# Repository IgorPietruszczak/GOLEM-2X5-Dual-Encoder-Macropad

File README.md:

# 🎮 GOLEM 2x5 Dual Encoder Macropad

An open-source 2x5 macropad featuring **dual rotary encoders**, a custom PCB, and fully 3D-printed case.

---

## ✨ Features

- **2×5 key grid** — 10 programmable keys
- **Dual rotary encoders** — for volume, scrolling, zoom, or any custom action
- **Pro Micro** microcontroller (ATmega32U4)
- **QMK firmware** — customizable layers, macros, and encoder mappings
- **Custom KiCad PCB** — open-source design files included
- **3D-printed case** — print-ready STL files included
- **MIT licensed** — free to use, modify, and share

---

## 📁 Repository Structure

```
GOLEM-2X5-Dual-Encoder-Macropad/
├── 3D Parts/                           # STL files for the case and knobs
├── Design Files For 3D Parts/          # KiCad schematics and PCB layout
├── PCB Design & Production files/      # Supporting design assets
├── QMK Keyboard Layout/                # QMK firmware source
├── LICENSE
└── README.md
```

---

## 🛒 Bill of Materials (BOM)

| Part | Quantity | Notes |
|------|----------|-------|
| Pro Micro (ATmega32U4) | 1 | USB-C version recommended |
| Rotary Encoder (EC11) | 2 | With push-button |
| Encoder Knobs | 2 | STL included, or use off-the-shelf |
| MX-compatible switches | 10 | 3-pin |
| 1N4148 Diodes | 10 | Through-hole |
| Keycaps | 10 | MX compatible |
| M2 screws 5mm & heat inserts | — | For case assembly |
| Custom PCB | 1 | Gerber files in `PCB Design & Production files/` |
| 3D-printed case | 1 set | STL files in `3D Parts/` |
| Silicone anti-slip pads | 4 | Placed in the corners on the bottom of the case |
| Tact Switch | 1 | For easy enabling of boot mode |

---

## 🖨️ 3D Printing

All STL files are located in the `3D Parts/` folder.

**Recommended settings:**
- Layer height: **0.2 mm**
- Infill: **15%**
- Supports: **No** (parts are designed to print without supports)
- Material: **PLA or PETG**

**Parts to print:**
- `Case_bottom.3mf` — Main keyboard body × 1
- `Encoder_Support.3mf` — Support to prevent bending the PCB while pressing the encoder button × 1
- `Knob_Edit_105_scaled.stl` — Knob for the standard rotary encoder × 2
- `PCB_Cover.stl` — Top PCB cover × 1

> The encoder knob model is adapted from [this Thingiverse design](https://www.thingiverse.com/thing:4206617/) — scaled up 5% to better fit EC11 encoders.

---

## 🔌 PCB & Wiring

PCB design files (KiCad) are located in the `PCB Design & Production files/` folder.
Ready Gerber files are located in the **production** folder.
Order PCB boards from the PCB manufacturer of your choosing.

**To open the project:**
1. Install [KiCad](https://www.kicad.org/) (version 7.0 or later recommended)
2. Open `Design_Files/*.kicad_pro`
3. Review the schematic

> KiCad component library courtesy of [@joe_scotto](https://www.youtube.com/@joe_scotto/featured) — this project is heavily inspired by this creator.

---

## 🔧 Assembly Guide

1. **Solder diodes to PCB** — Pay attention to soldering them with the correct polarity. Check the KiCad project or PCB 3D model for reference.
2. **Solder Pro Micro to PCB** — The project is designed to use the pin arrays that come with the microcontroller. Check the PCB 3D model for reference.
3. **Solder tact switch to PCB.**
4. **Place MX switches into holes on PCB Cover 3D print** — Pay attention to placing them in the correct orientation.
5. **Solder MX switches to PCB** — After this step the PCB cover is unremovable, so be sure to complete all prior steps correctly.
6. **Solder 2 rotary encoders to PCB** — Make sure they sit flat and stable before soldering.
7. **Insert heat inserts into designated places on Bottom Cover.**
8. **Screw PCB to bottom cover with M2 screws.**
9. **Place keycaps on MX switches and knobs on rotary encoders.**
10. **Stick silicone pads to the bottom of the Bottom Cover.**

---

## ⚡ Firmware Setup (QMK)

This keyboard uses QMK firmware. Here are some tutorials on how to set up the keyboard layout:

- [Tutorial 1](https://www.youtube.com/watch?v=fuBJbdCFF0Q&t=241s)
- [Tutorial 2](https://www.youtube.com/watch?v=hjml-K-pV4E&t=1155s)

### Quick Setup

1. **Install QMK Firmware** — QMK MSYS, QMK Toolbox, drivers, etc.
2. **Move the keyboard layout** from `QMK Keyboard Layout/` to your keyboards folder in QMK.
3. **Flash the GOLEM 2x5 keyboard layout using QMK Toolbox** — Enable flash mode using the tact switch on the keyboard.
4. **Edit the keyboard layout (optional)** — Open `golem_2x5_dualencoder_macropad/` in a text editor and edit the keyboard settings.

---

## 🤝 Contributing

Contributions are welcome! Feel free to:
- Open an **Issue** for bugs or suggestions
- Submit a **Pull Request** with improvements
- Share your build photos — I'd love to see them!

---

## 📄 License

This project is licensed under the **MIT License** — see the [LICENSE](LICENSE) file for details.

---

## 🙏 Credits

- Encoder knob 3D model by [Thingiverse user](https://www.thingiverse.com/thing:4206617/)
- KiCad component library by [@joe_scotto](https://www.youtube.com/@joe_scotto/featured)

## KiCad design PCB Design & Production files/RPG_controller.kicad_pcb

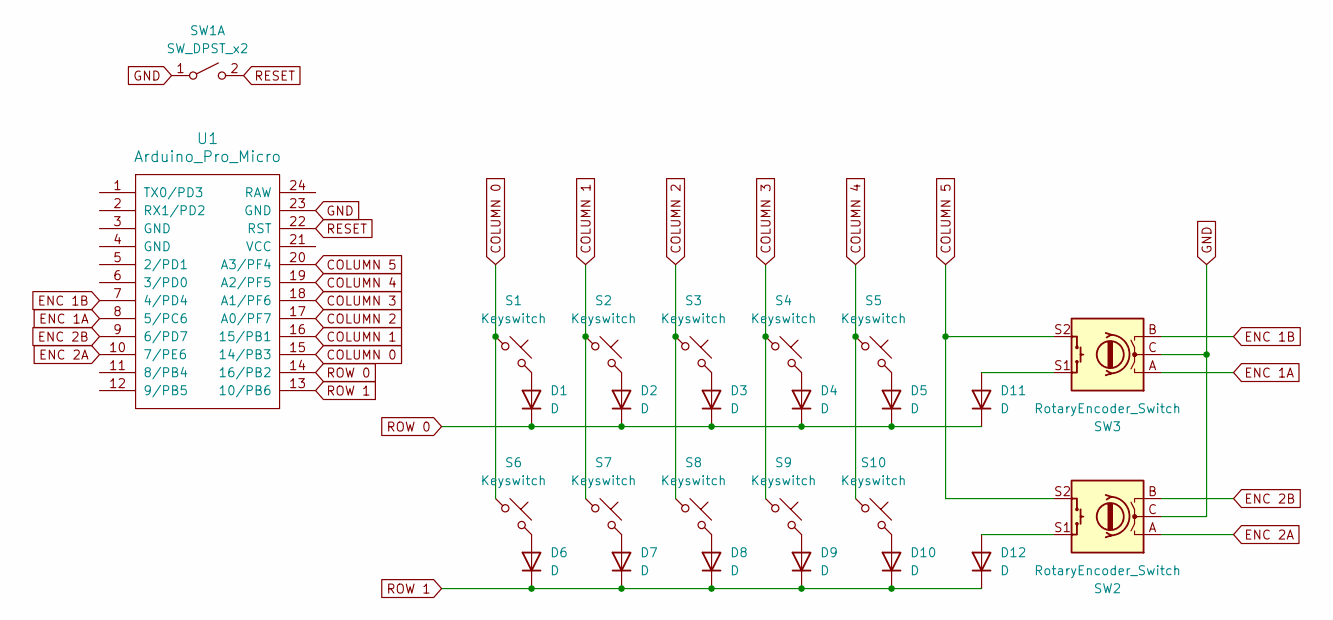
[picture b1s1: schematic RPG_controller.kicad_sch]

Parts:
D1, D2, D3, D4, D5, D6, D7, D8, D9, D10, D11, D12: D; Diode_DO-35
S1, S2, S3, S4, S5, S6, S7, S8, S9, S10: Keyswitch; SW_Cherry_MX_1.00u_PCB
SW1: SW_DPST_x2; SW_TH_Tactile_Omron_B3F-10xx
SW2, SW3: RotaryEncoder_Switch; RotaryEncoder_Alps_EC11E-Switch_Vertical_H20mm
U1: Arduino_Pro_Micro

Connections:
COLUMN 0: S1.1, S6.1, U1.15 (14/PB3)
COLUMN 1: S2.1, S7.1, U1.16 (15/PB1)
COLUMN 2: S3.1, S8.1, U1.17 (A0/PF7)
COLUMN 3: S4.1, S9.1, U1.18 (A1/PF6)
COLUMN 4: S5.1, S10.1, U1.19 (A2/PF5)
COLUMN 5: SW2.S2, SW3.S2, U1.20 (A3/PF4)
ENC 1A: SW3.A, U1.8 (5/PC6)
ENC 1B: SW3.B, U1.7 (4/PD4)
ENC 2A: SW2.A, U1.10 (7/PE6)
ENC 2B: SW2.B, U1.9 (6/PD7)
GND: SW1.1 (A), SW2.C, SW3.C, U1.23 (GND)
unnamed: D1.2 (A), S1.2
unnamed: D2.2 (A), S2.2
unnamed: D3.2 (A), S3.2
unnamed: D4.2 (A), S4.2
unnamed: D5.2 (A), S5.2
unnamed: D6.2 (A), S6.2
unnamed: D7.2 (A), S7.2
unnamed: D8.2 (A), S8.2
unnamed: D9.2 (A), S9.2
unnamed: D10.2 (A), S10.2
unnamed: D11.2 (A), SW3.S1
unnamed: D12.2 (A), SW2.S1
RESET: SW1.2 (B), U1.22 (RST)
ROW 0: D1.1 (K), D2.1 (K), D3.1 (K), D4.1 (K), D5.1 (K), D11.1 (K), U1.14 (16/PB2)
ROW 1: D6.1 (K), D7.1 (K), D8.1 (K), D9.1 (K), D10.1 (K), D12.1 (K), U1.13 (10/PB6)

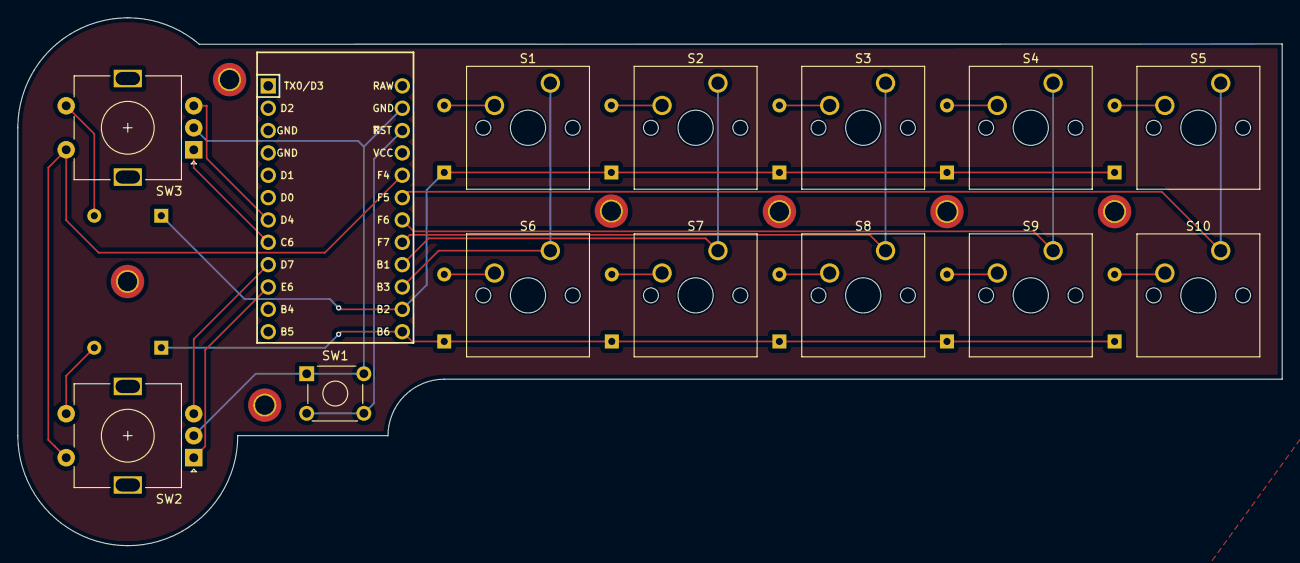
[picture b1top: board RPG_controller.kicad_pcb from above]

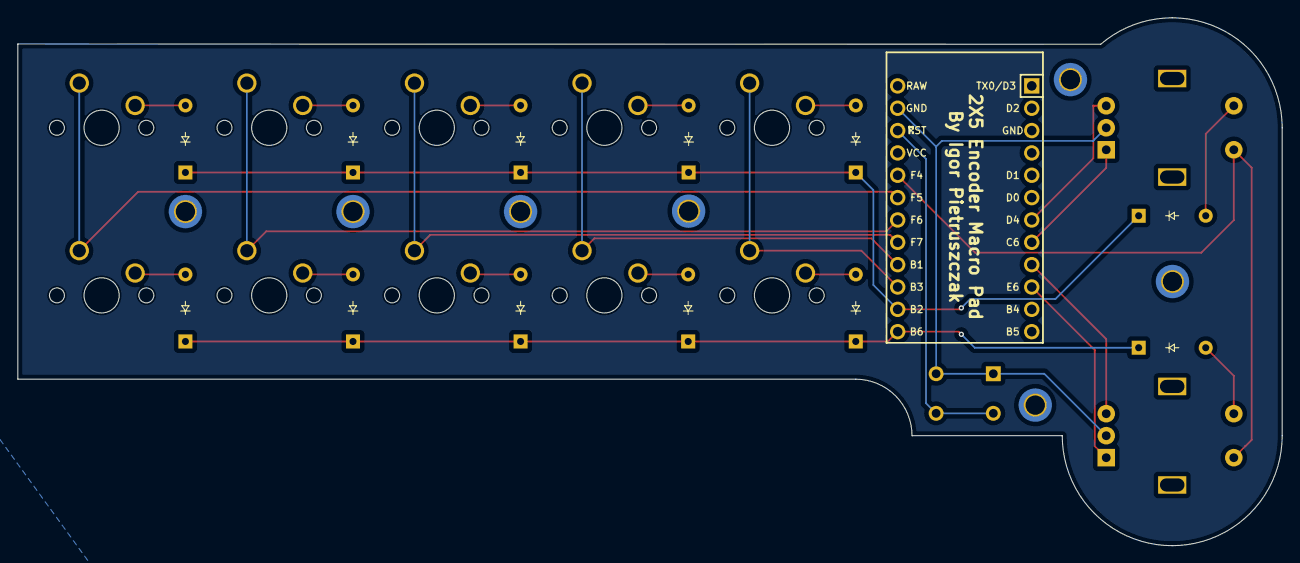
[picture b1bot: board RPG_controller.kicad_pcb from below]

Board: 2 copper layers, 143.7 x 60.0 mm, 26 parts (12 on the bottom side), 26 nets.

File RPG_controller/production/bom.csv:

Designator,Footprint,Quantity,Value,LCSC Part #
"D1, D10, D11, D12, D2, D3, D4, D5, D6, D7, D8, D9",Diode_DO-35,12,D,
"S1, S10, S2, S3, S4, S5, S6, S7, S8, S9",SW_Cherry_MX_1.00u_PCB,10,Keyswitch,
SW1,SW_TH_Tactile_Omron_B3F-10xx,1,SW_DPST_x2,
"SW2, SW3",RotaryEncoder_Alps_EC11E-Switch_Vertical_H20mm,2,RotaryEncoder_Switch,
U1,Arduino_Pro_Micro,1,Arduino_Pro_Micro,

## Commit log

2025-07-11 Project files upload
2025-07-11 Adding links to people that helped make this project possible
2026-05-05 Fixing organization and folder structure
2026-05-05 Update README with build images and structure
    Added images of the finished build and updated the README structure.

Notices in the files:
README.md:
License: MIT
